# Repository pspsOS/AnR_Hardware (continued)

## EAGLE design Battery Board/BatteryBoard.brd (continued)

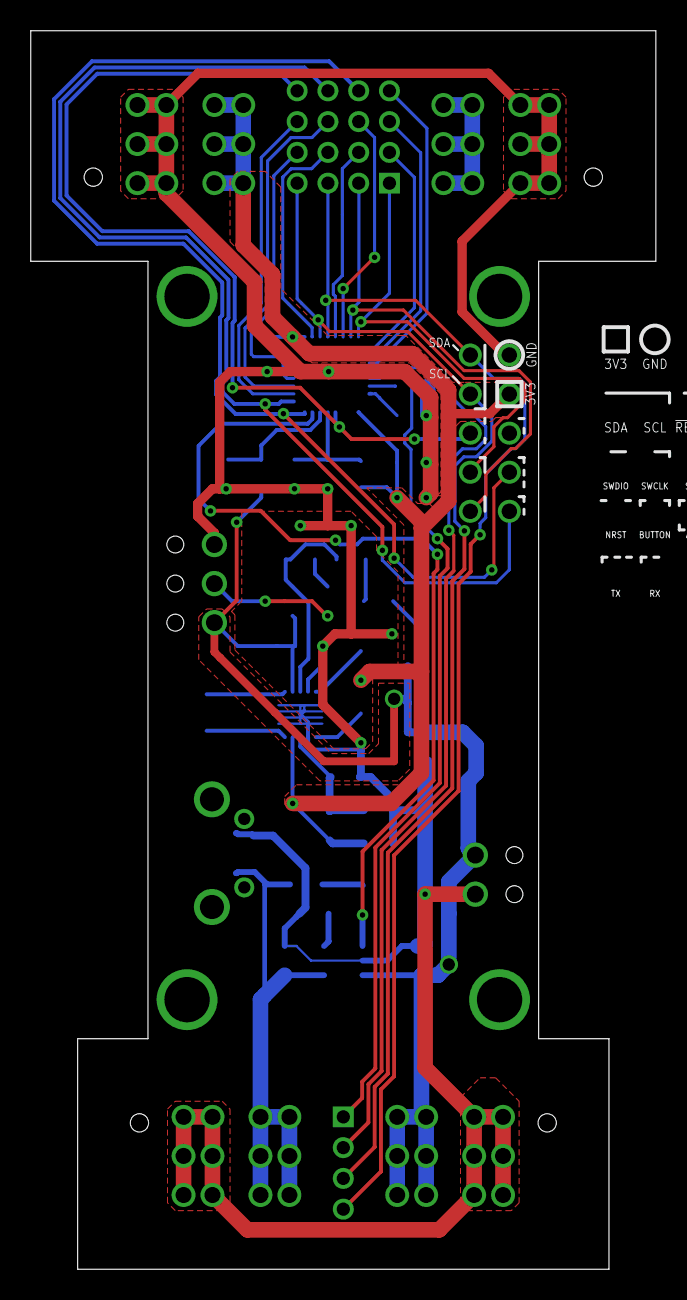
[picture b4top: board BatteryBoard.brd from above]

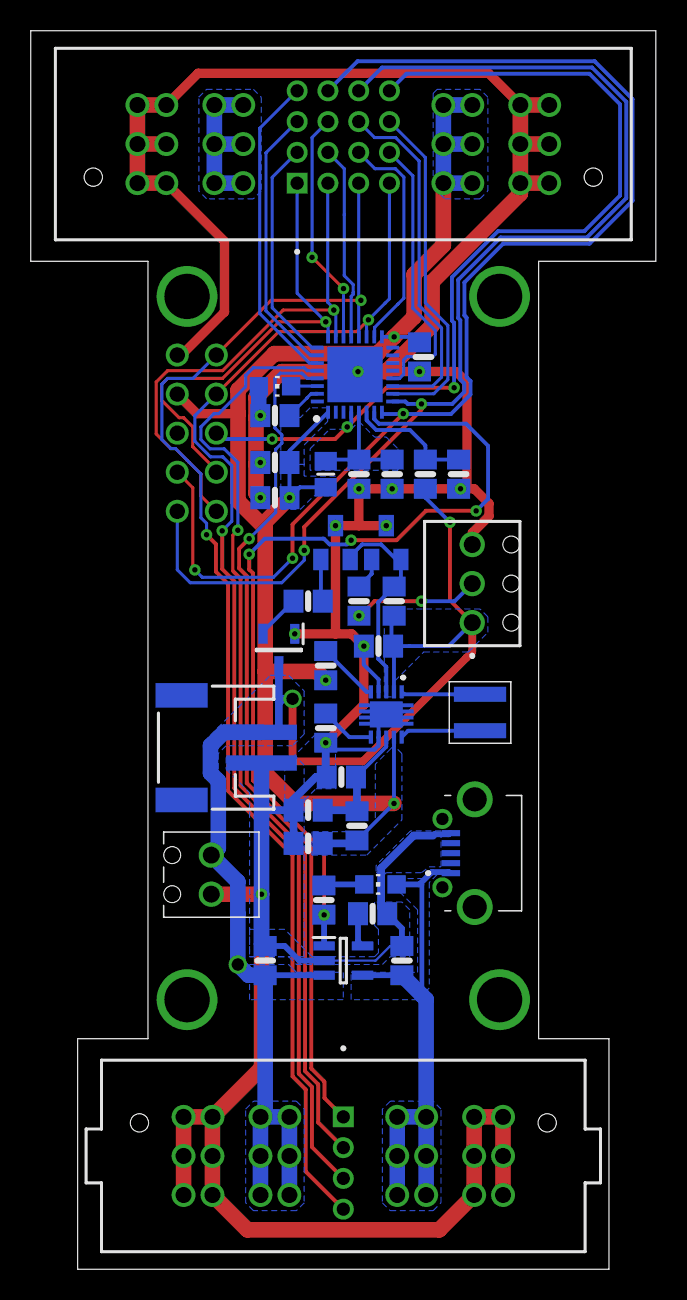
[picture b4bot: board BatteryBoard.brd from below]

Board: 2 copper layers, 40.6 x 80.5 mm, 38 parts (38 on the bottom side), 40 nets.

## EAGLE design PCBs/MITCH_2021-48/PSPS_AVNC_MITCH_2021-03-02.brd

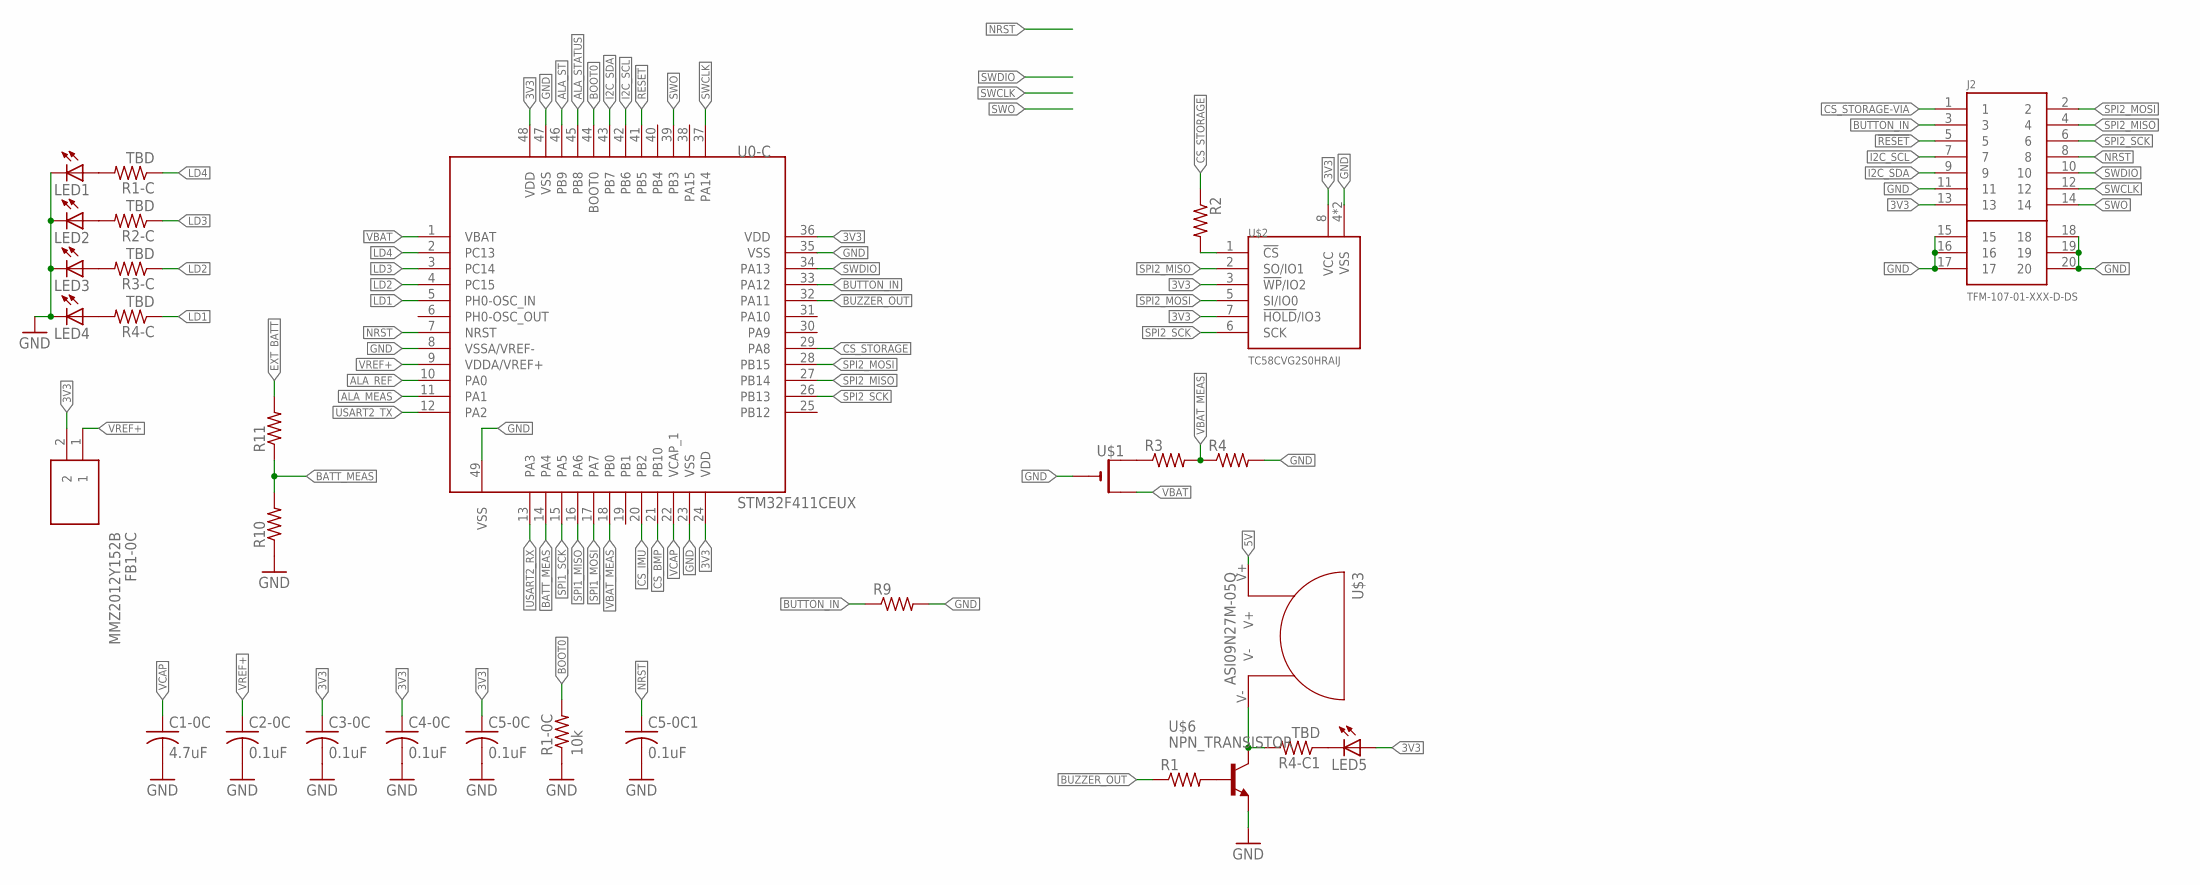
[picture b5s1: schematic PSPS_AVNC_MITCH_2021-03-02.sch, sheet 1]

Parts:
C1-0C: 4.7uF; C0805
C2-0C, C3-0C, C4-0C, C5-0C, C5-0C1: 0.1uF; C0805
FB1-0C: MMZ2012Y152B; BEADC2012X105N
J2: TFM-107-01-XXX-D-DS
LED1, LED2, LED3, LED4, LED5: LEDCHIPLED_0805; CHIPLED_0805
R1, R2, R3, R4, R9, R10, R11: R-US_R0805; R0805
R1-0C: 10k; R0805
R1-C, R2-C, R3-C, R4-C, R4-C1: TBD; R0805
U0-C: STM32F411CEUX; QFN50P700X700X50-49T560N
U$1: CR1220SMT; CR1220-SMD
U$2: TC58CVG2S0HRAIJ; SON127P800X600X80-9T350X440N
U$3: ASI09N27M-05Q
U$6: NPN_TRANSISTOR; SOT23

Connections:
3V3: C3-0C.1, C4-0C.1, C5-0C.1, FB1-0C.2, J2.13, LED5.A, U0-C.24 (VDD), U0-C.36 (VDD), U0-C.48 (VDD), U$2.3 (!WP!/IO2), U$2.7 (!HOLD!/IO3), U$2.8 (VCC); also elsewhere on the board
5V: U$3.V+; also elsewhere on the board
!RESET!: J2.5, U0-C.41 (PB5)
ALA_MEAS: U0-C.11 (PA1); also elsewhere on the board
ALA_REF: U0-C.10 (PA0); also elsewhere on the board
ALA_ST: U0-C.46 (PB9); also elsewhere on the board
ALA_STATUS: U0-C.45 (PB8); also elsewhere on the board
BATT_MEAS: R10.2, R11.1, U0-C.14 (PA4)
BOOT0: R1-0C.2, U0-C.44 (BOOT0)
BUTTON_IN: J2.3, R9.1, U0-C.33 (PA12)
BUZZER_OUT: R1.1, U0-C.32 (PA11)
CS_BMP: U0-C.21 (PB10); also elsewhere on the board
CS_IMU: U0-C.20 (PB2); also elsewhere on the board
CS_STORAGE: R2.1, U0-C.29 (PA8)
CS_STORAGE-VIA: J2.1, R2.2, U$2.1 (!CS!)
EXT_BATT: R11.2
GND: C1-0C.2, C2-0C.2, C3-0C.2, C4-0C.2, C5-0C.2, C5-0C1.2, J2.11, J2.15, J2.16, J2.17, J2.18, J2.19, J2.20, LED1.C, LED2.C, LED3.C, LED4.C, R1-0C.1, R4.2, R9.2, R10.1, U0-C.8 (VSSA/VREF-), U0-C.23 (VSS), U0-C.35 (VSS), U0-C.47 (VSS), U0-C.49 (VSS), U$1.-, U$2.4 (VSS), U$2.9 (VSS), U$6.3 (E); also elsewhere on the board
I2C_SCL: J2.7, U0-C.42 (PB6)
I2C_SDA: J2.9, U0-C.43 (PB7)
LD1: R4-C.1, U0-C.5 (PH0-OSC_IN)
LD2: R3-C.1, U0-C.4 (PC15)
LD3: R2-C.1, U0-C.3 (PC14)
LD4: R1-C.1, U0-C.2 (PC13)
unnamed: R1.2, U$6.1 (B)
unnamed: LED4.A, R4-C.2
unnamed: LED3.A, R3-C.2
unnamed: LED2.A, R2-C.2
unnamed: LED1.A, R1-C.2
unnamed: R3.1, U$1.+$1 (+)
unnamed: R4-C1.2, U$3.V-, U$6.2 (C)
unnamed: LED5.C, R4-C1.1
NRST: C5-0C1.1, J2.8, U0-C.7 (NRST)
SPI1_MISO: U0-C.16 (PA6); also elsewhere on the board
SPI1_MOSI: U0-C.17 (PA7); also elsewhere on the board
SPI1_SCK: U0-C.15 (PA5); also elsewhere on the board
SPI2_MISO: J2.4, U0-C.27 (PB14), U$2.2 (SO/IO1)
SPI2_MOSI: J2.2, U0-C.28 (PB15), U$2.5 (SI/IO0)
SPI2_SCK: J2.6, U0-C.26 (PB13), U$2.6 (SCK)
SWCLK: J2.12, U0-C.37 (PA14)
SWDIO: J2.10, U0-C.34 (PA13)
SWO: J2.14, U0-C.39 (PB3)
USART2_RX: U0-C.13 (PA3); also elsewhere on the board
USART2_TX: U0-C.12 (PA2); also elsewhere on the board
VBAT: U0-C.1 (VBAT), U$1.+$2 (+1); also elsewhere on the board
VBAT_MEAS: R3.2, R4.1, U0-C.18 (PB0)
VCAP: C1-0C.1, U0-C.22 (VCAP_1)
VREF+: C2-0C.1, FB1-0C.1, U0-C.9 (VDDA/VREF+)

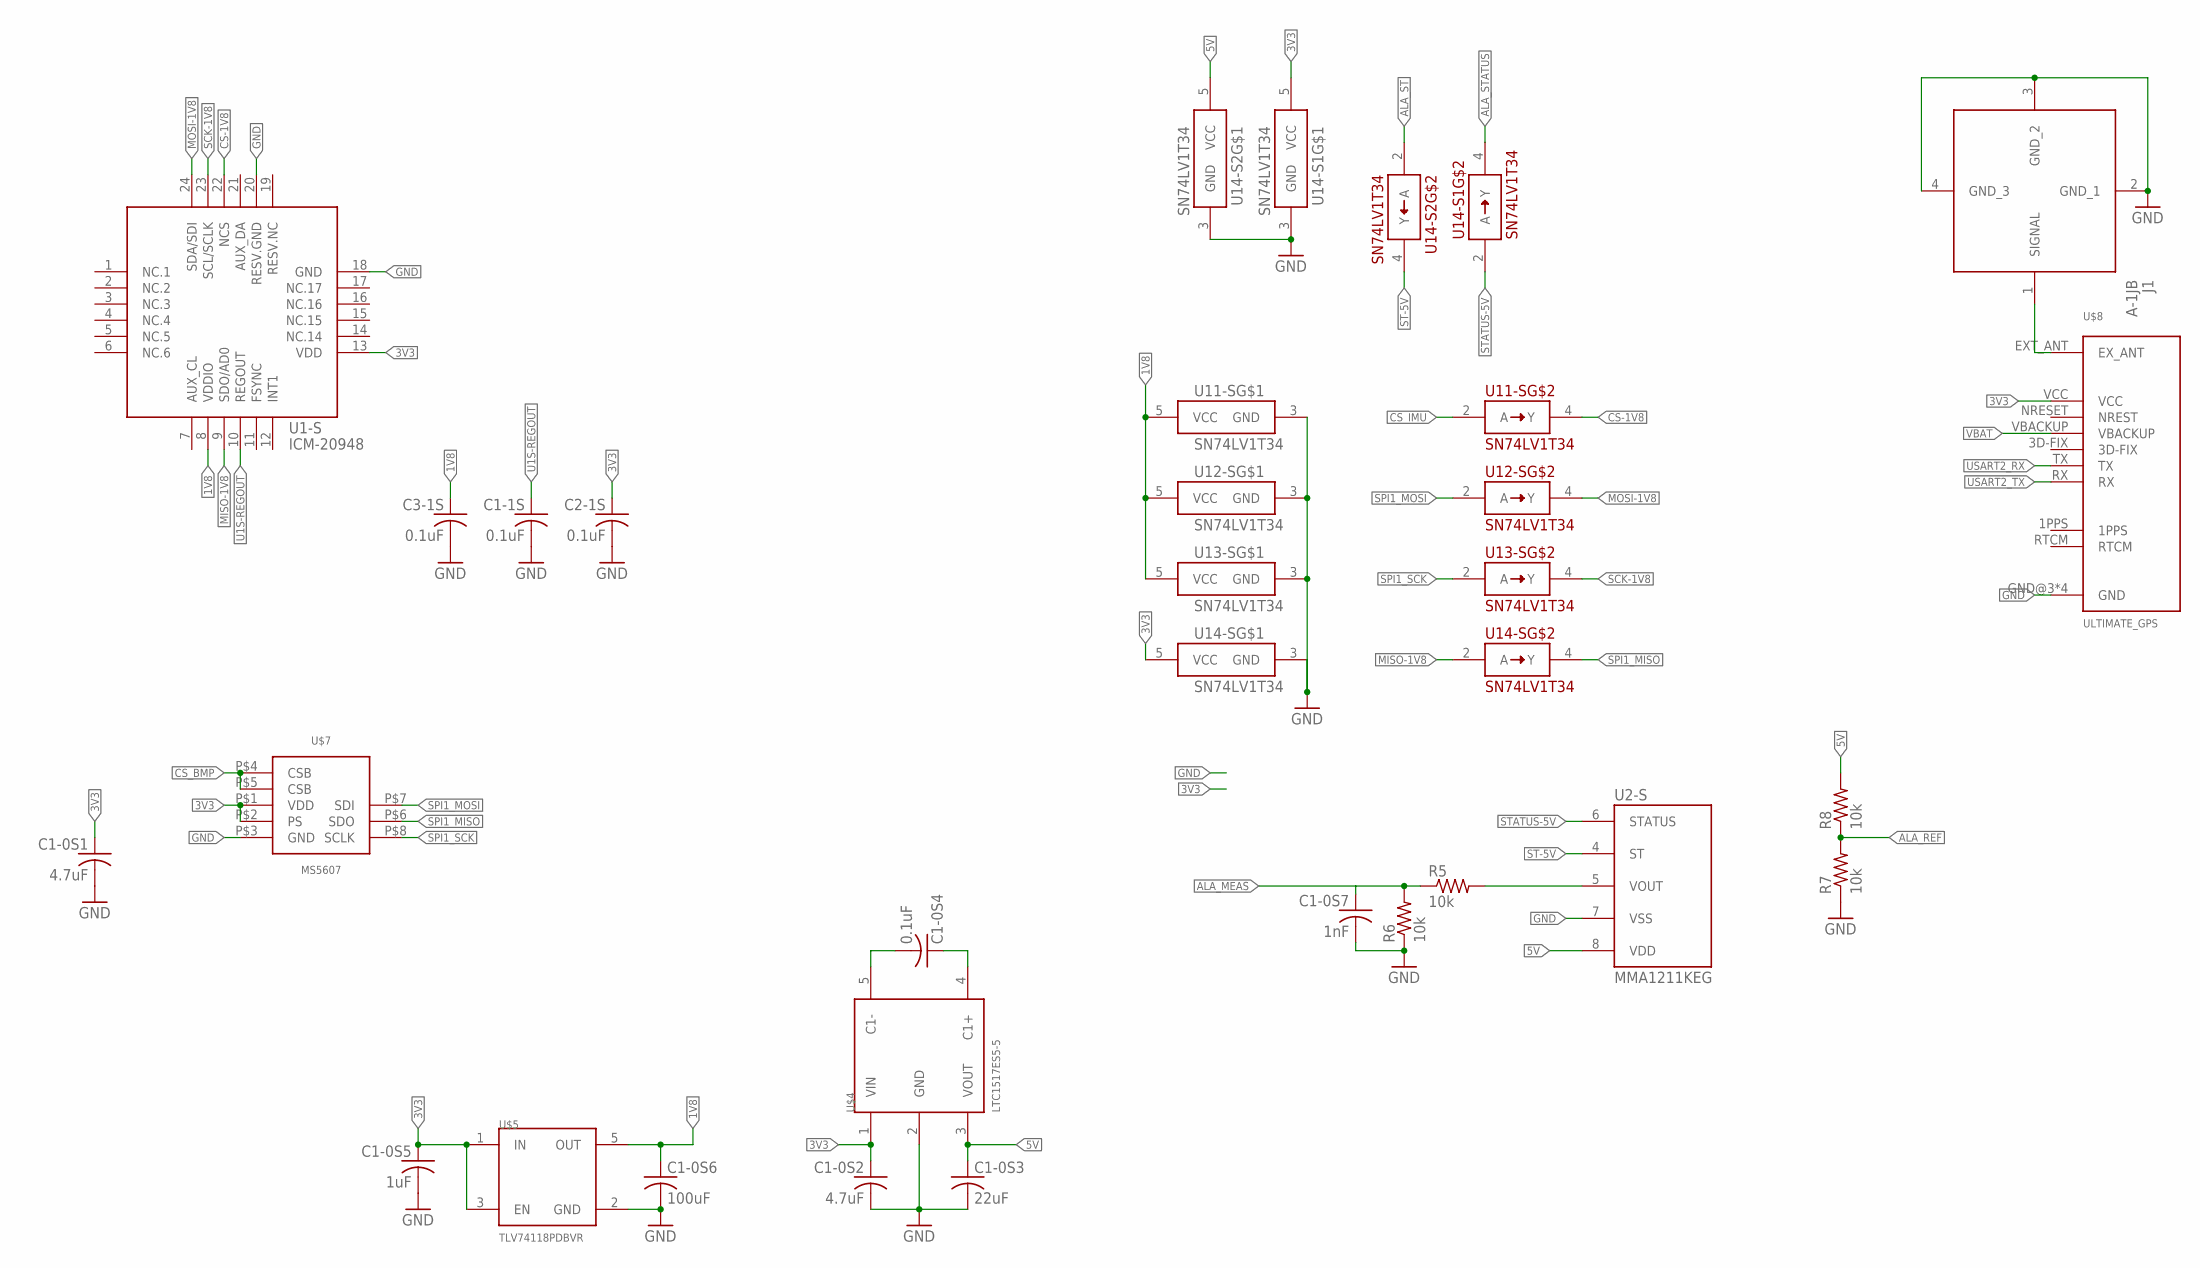
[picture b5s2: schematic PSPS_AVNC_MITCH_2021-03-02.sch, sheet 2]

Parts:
C1-0S1, C1-0S2: 4.7uF; C0805
C1-0S3: 22uF; C0805
C1-0S4, C1-1S, C2-1S, C3-1S: 0.1uF; C0805
C1-0S5: 1uF; C0805
C1-0S6: 100uF; C0805
C1-0S7: 1nF; C0805
J1: A-1JB; A1JB
R5, R6, R7, R8: 10k; R0805
U1-S: ICM-20948; QFN40P300X300X105-25T159X175
U2-S: MMA1211KEG; SOIC127P1041X355-16N
U11-S, U12-S, U13-S, U14-S, U14-S1, U14-S2: SN74LV1T34; SOT65P210X110-5
U$4: LTC1517ES5-5; SOT95P280X145-5N
U$5: TLV74118PDBVR; SOT95P280X145-5N
U$7: MS5607
U$8: ULTIMATE_GPS; FGPMMOPA6H

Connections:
1V8: C1-0S6.1, C3-1S.1, U1-S.8 (VDDIO), U11-S.5 (VCC), U12-S.5 (VCC), U13-S.5 (VCC), U$5.5 (OUT)
3V3: C1-0S1.1, C1-0S2.1, C1-0S5.1, C2-1S.1, U1-S.13 (VDD), U14-S.5 (VCC), U14-S1.5 (VCC), U$4.1 (VIN), U$5.1 (IN), U$5.3 (EN), U$7.P$1 (VDD), U$7.P$2 (PS), U$8.VCC; also elsewhere on the board
5V: C1-0S3.1, R8.2, U2-S.8 (VDD), U14-S2.5 (VCC), U$4.3 (VOUT); also elsewhere on the board
ALA_MEAS: C1-0S7.1, R5.1, R6.2; also elsewhere on the board
ALA_REF: R7.2, R8.1; also elsewhere on the board
ALA_ST: U14-S2.2 (A); also elsewhere on the board
ALA_STATUS: U14-S1.4 (Y); also elsewhere on the board
CS-1V8: U1-S.22 (NCS), U11-S.4 (Y)
CS_BMP: U$7.P$4 (CSB), U$7.P$5 (CSB); also elsewhere on the board
CS_IMU: U11-S.2 (A); also elsewhere on the board
GND: C1-0S1.2, C1-0S2.2, C1-0S3.2, C1-0S5.2, C1-0S6.2, C1-0S7.2, C1-1S.2, C2-1S.2, C3-1S.2, J1.2 (GND_1), J1.3 (GND_2), J1.4 (GND_3), R6.1, R7.1, U1-S.18 (GND), U1-S.20 (RESV.GND), U2-S.7 (VSS), U11-S.3 (GND), U12-S.3 (GND), U13-S.3 (GND), U14-S.3 (GND), U14-S1.3 (GND), U14-S2.3 (GND), U$4.2 (GND), U$5.2 (GND), U$7.P$3 (GND), U$8.GND@3 (GND), U$8.GND@8 (GND), U$8.GND@12 (GND), U$8.GND@19 (GND); also elsewhere on the board
MISO-1V8: U1-S.9 (SDO/AD0), U14-S.2 (A)
MOSI-1V8: U1-S.24 (SDA/SDI), U12-S.4 (Y)
unnamed: C1-0S4.1, U$4.4 (C1+)
unnamed: C1-0S4.2, U$4.5 (C1-)
unnamed: J1.1 (SIGNAL), U$8.EXT_ANT (EX_ANT)
unnamed: R5.2, U2-S.5 (VOUT)
SCK-1V8: U1-S.23 (SCL/SCLK), U13-S.4 (Y)
SPI1_MISO: U14-S.4 (Y), U$7.P$6 (SDO); also elsewhere on the board
SPI1_MOSI: U12-S.2 (A), U$7.P$7 (SDI); also elsewhere on the board
SPI1_SCK: U13-S.2 (A), U$7.P$8 (SCLK); also elsewhere on the board
ST-5V: U2-S.4 (ST), U14-S2.4 (Y)
STATUS-5V: U2-S.6 (STATUS), U14-S1.2 (A)
U1S-REGOUT: C1-1S.1, U1-S.10 (REGOUT)
USART2_RX: U$8.TX; also elsewhere on the board
USART2_TX: U$8.RX; also elsewhere on the board
VBAT: U$8.VBACKUP; also elsewhere on the board

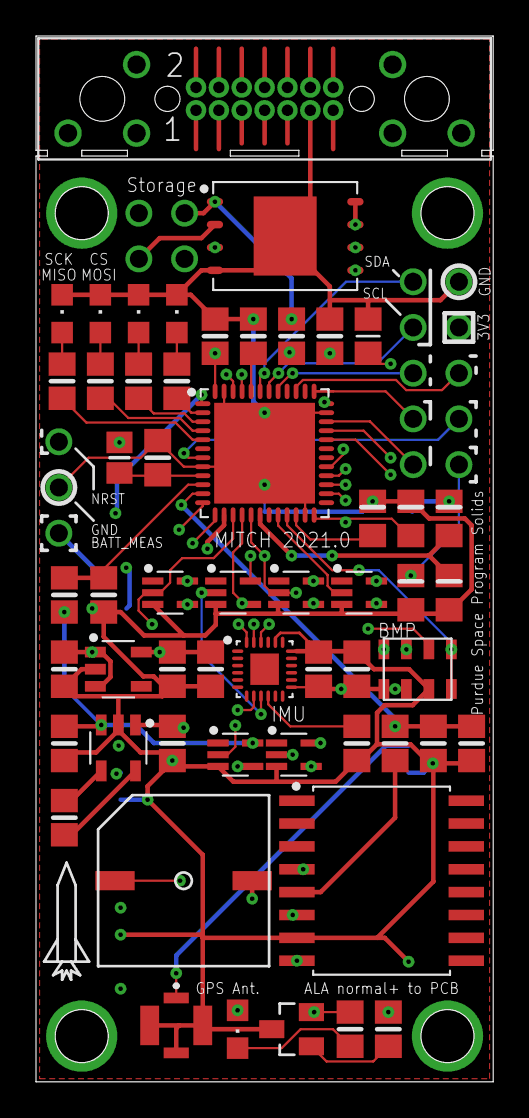
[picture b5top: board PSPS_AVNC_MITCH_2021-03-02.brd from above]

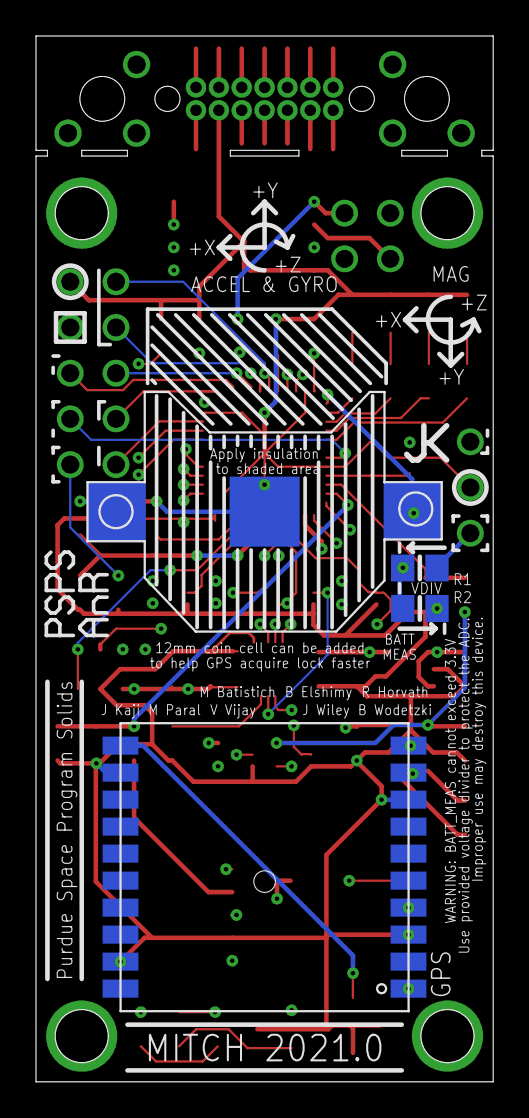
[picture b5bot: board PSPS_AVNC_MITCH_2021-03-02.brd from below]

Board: 4 copper layers, 25.4 x 58.1 mm, 58 parts (4 on the bottom side), 58 nets.

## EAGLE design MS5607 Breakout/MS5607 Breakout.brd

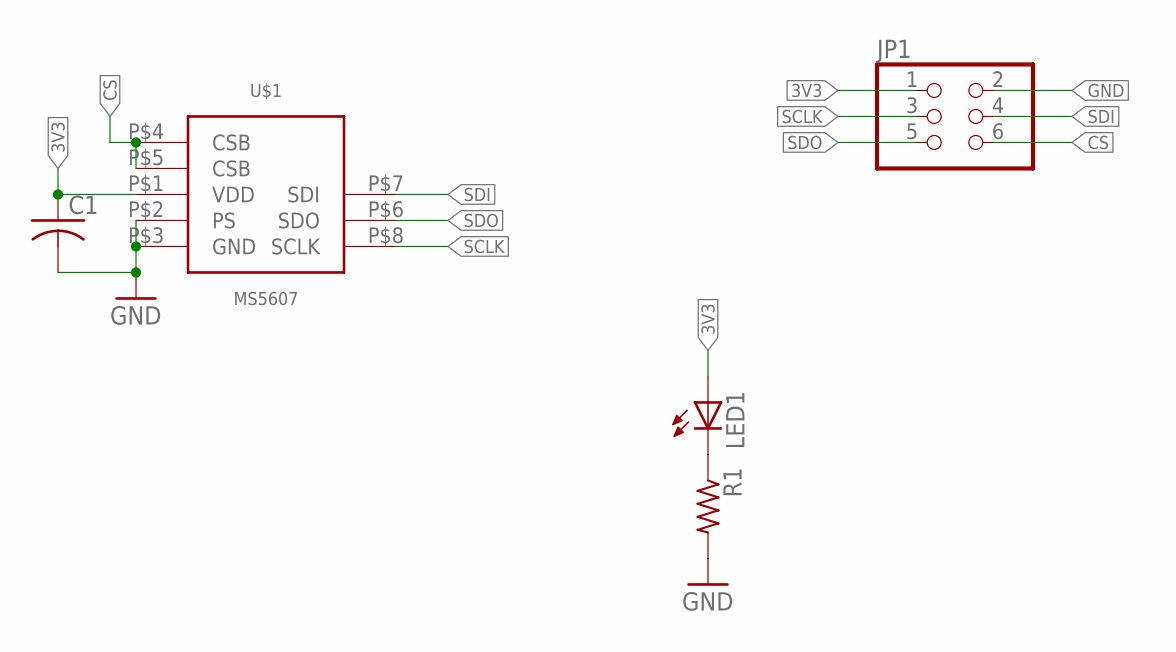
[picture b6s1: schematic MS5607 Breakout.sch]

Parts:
C1: C-USC0805; C0805
JP1: PINHD-2X3; 2X03
LED1: LEDCHIPLED_0805; CHIPLED_0805
R1: R-US_R0805; R0805
U$1: MS5607

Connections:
3V3: C1.1, JP1.1, LED1.A, U$1.P$1 (VDD)
CS: JP1.6, U$1.P$4 (CSB), U$1.P$5 (CSB)
GND: C1.2, JP1.2, R1.2, U$1.P$2 (PS), U$1.P$3 (GND)
unnamed: LED1.C, R1.1
SCLK: JP1.3, U$1.P$8 (SCLK)
SDI: JP1.4, U$1.P$7 (SDI)
SDO: JP1.5, U$1.P$6 (SDO)

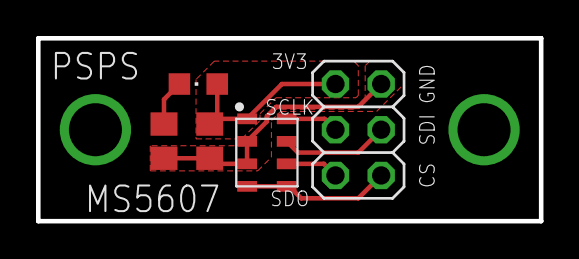
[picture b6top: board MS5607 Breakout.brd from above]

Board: 2 copper layers, 27.9 x 10.2 mm, 5 parts (0 on the bottom side), 7 nets.

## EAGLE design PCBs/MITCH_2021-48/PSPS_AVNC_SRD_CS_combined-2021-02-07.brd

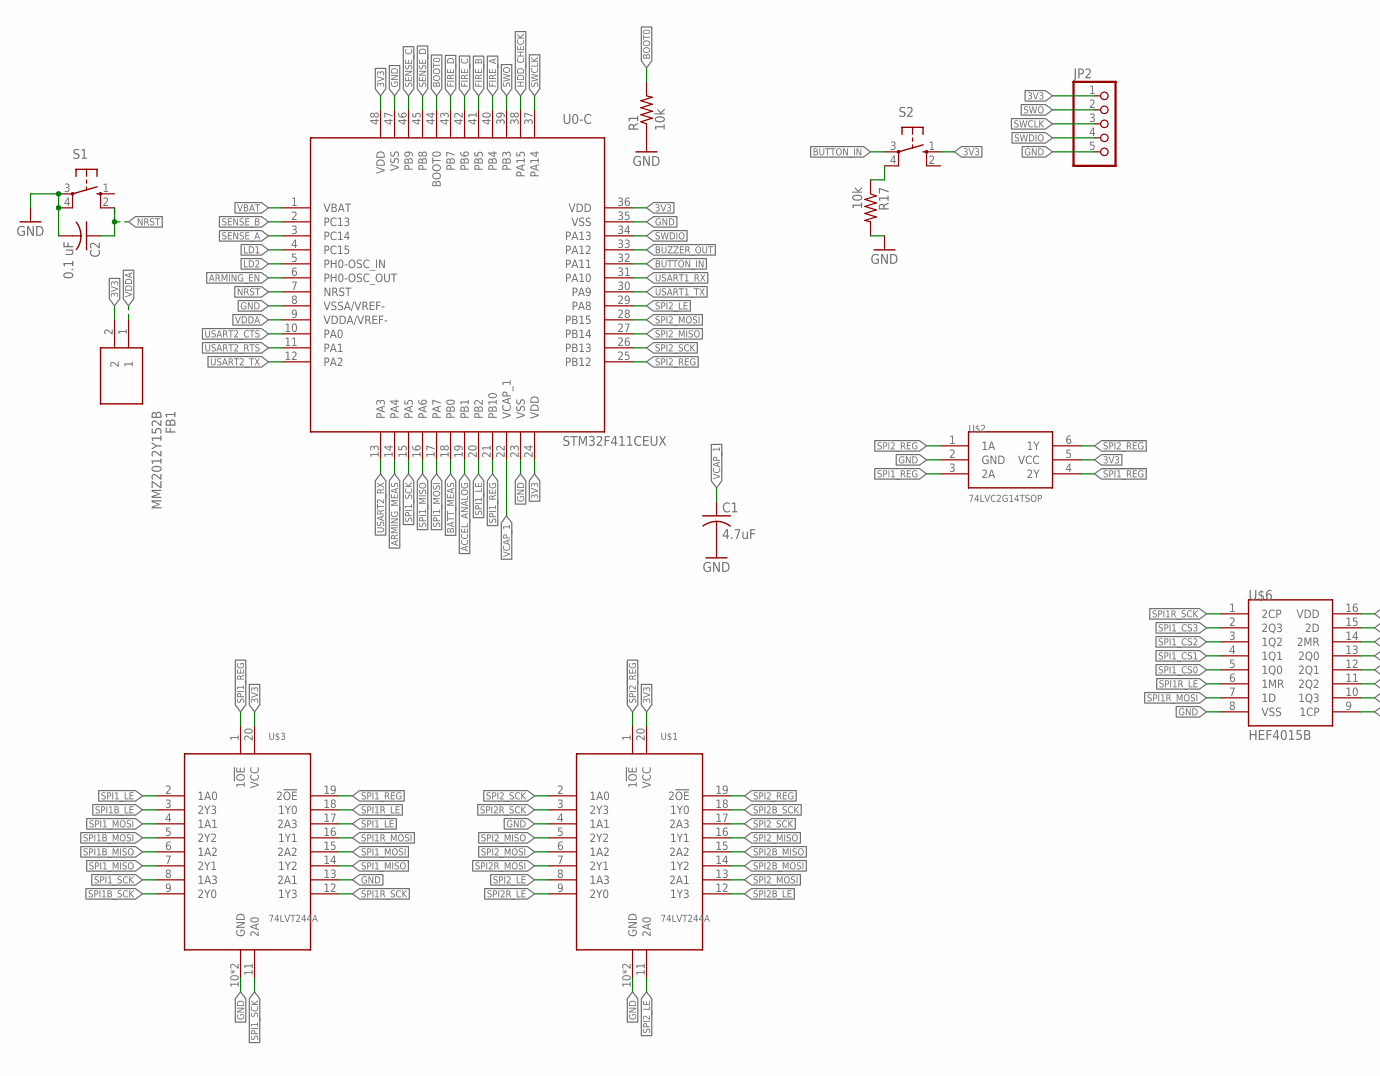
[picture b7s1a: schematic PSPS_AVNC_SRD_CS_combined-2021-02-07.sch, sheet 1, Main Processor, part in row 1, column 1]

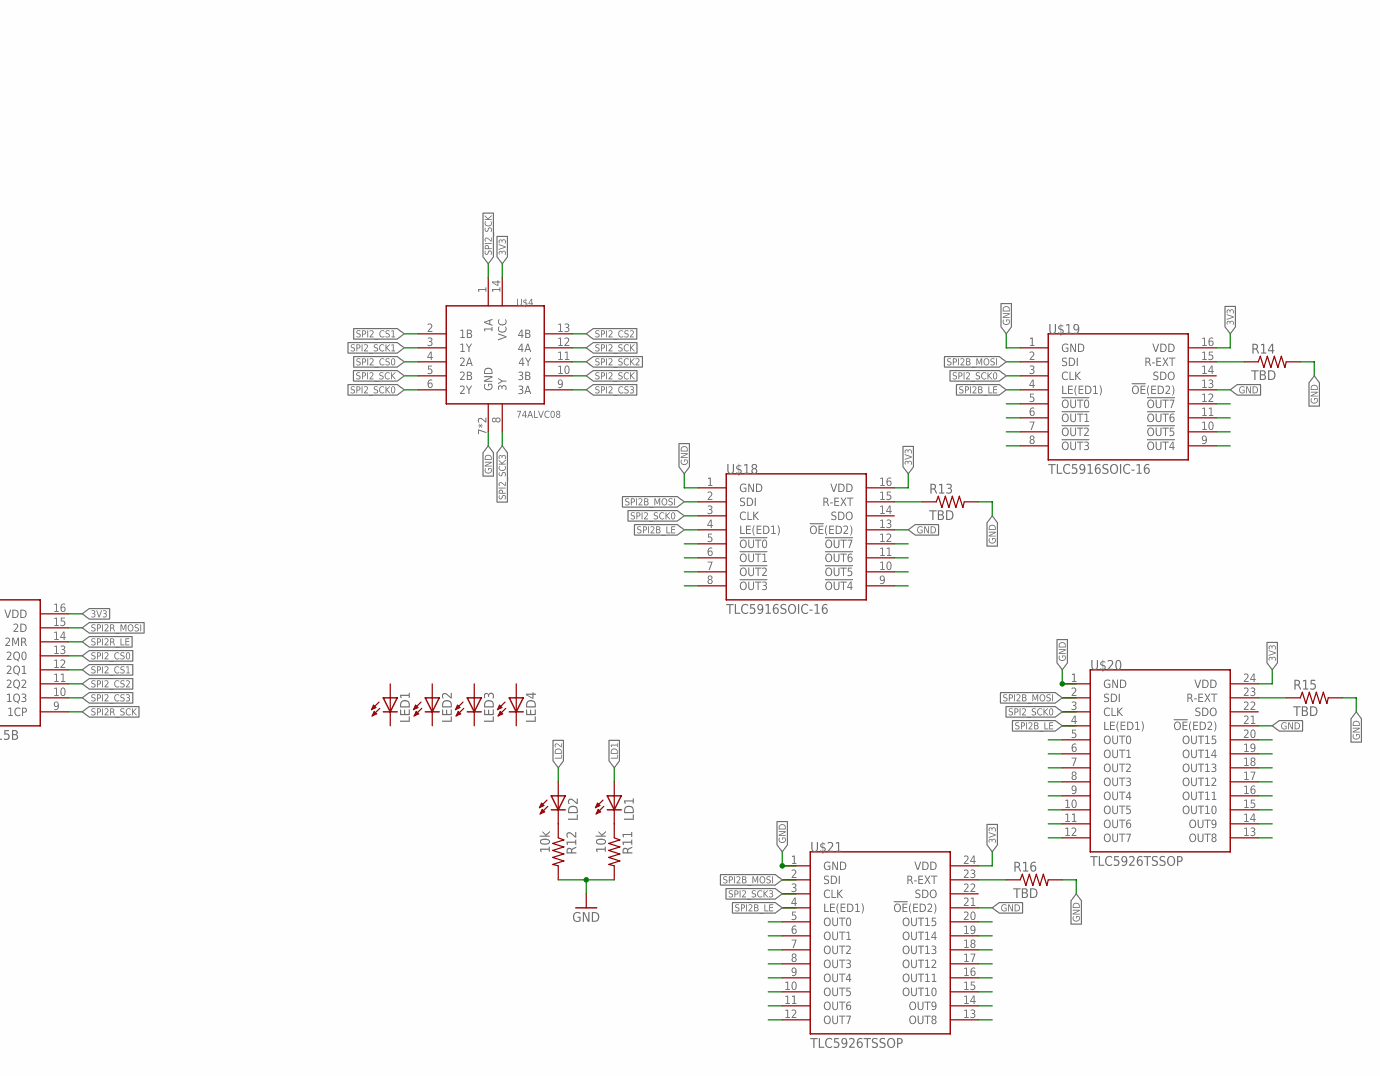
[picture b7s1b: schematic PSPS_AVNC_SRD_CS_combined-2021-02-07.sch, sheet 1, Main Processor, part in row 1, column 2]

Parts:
C1: 4.7uF; C0805
C2: 0.1 uF; C0805
FB1: MMZ2012Y152B; BEADC2012X105N
JP2: PINHD-1X5; 1X05
LD1, LD2: LEDCHIP-LED0805; CHIP-LED0805
LED1, LED2, LED3, LED4: LEDCHIP-LED0805; CHIP-LED0805
R1, R11, R12, R17: 10k; M0805
R13, R14, R15, R16: TBD; M0805
S1, S2: 10-XX; B3F-10XX
U0-C: STM32F411CEUX; QFN50P700X700X50-49T560N
U$1, U$3: 74LVT244A; QFN50P450X250X100-21T300X100N
U$2: 74LVC2G14TSOP; SOP95P280X110-6N
U$4: 74ALVC08; QFN50P300X250X100-15T150X100N
U$6: HEF4015B; SOIC127P600X265-16N
U$18, U$19: TLC5916SOIC-16; SOIC127P600X175-16N
U$20, U$21: TLC5926TSSOP; SOP65P640X120-24N

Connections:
3V3: FB1.2, JP2.1, S2.1 (S), U0-C.24 (VDD), U0-C.36 (VDD), U0-C.48 (VDD), U$1.20 (VCC), U$2.5 (VCC), U$3.20 (VCC), U$4.14 (VCC), U$6.16 (VDD), U$18.16 (VDD), U$19.16 (VDD), U$20.24 (VDD), U$21.24 (VDD); also elsewhere on the board
!SPI1_REG!: U$2.4 (2Y), U$3.19 (2!OE!)
!SPI2_REG!: U$1.1 (1!OE!), U$2.6 (1Y)
ACCEL_ANALOG: U0-C.19 (PB1); also elsewhere on the board
ARMING_EN: U0-C.6 (PH0-OSC_OUT)
ARMING_MEAS: U0-C.14 (PA4)
BATT_MEAS: U0-C.18 (PB0)
BOOT0: R1.2, U0-C.44 (BOOT0)
BUTTON_IN: S2.3, U0-C.32 (PA11)
BUZZER_OUT: U0-C.33 (PA12); also elsewhere on the board
FIRE_A: U0-C.40 (PB4)
FIRE_B: U0-C.41 (PB5)
FIRE_C: U0-C.42 (PB6)
FIRE_D: U0-C.43 (PB7)
GND: C1.2, C2.2, JP2.5, R1.1, R11.2, R12.2, R13.2, R14.2, R15.2, R16.2, R17.2, S1.3, S1.4 (P1), U0-C.8 (VSSA/VREF-), U0-C.23 (VSS), U0-C.35 (VSS), U0-C.47 (VSS), U$1.4 (1A1), U$1.10 (GND), U$1.21 (GND), U$2.2 (GND), U$3.10 (GND), U$3.13 (2A1), U$3.21 (GND), U$4.7 (GND), U$4.15 (GND), U$6.8 (VSS), U$18.1 (GND), U$18.13 (!OE!(ED2)), U$19.1 (GND), U$19.13 (!OE!(ED2)), U$20.1 (GND), U$20.21 (!OE!(ED2)), U$21.1 (GND), U$21.21 (!OE!(ED2)); also elsewhere on the board
HDD_CHECK: U0-C.38 (PA15)
LD1: LD1.A, U0-C.4 (PC15)
LD2: LD2.A, U0-C.5 (PH0-OSC_IN)
unnamed: LD1.C, R11.1
unnamed: LD2.C, R12.1
unnamed: R13.1, U$18.15 (R-EXT)
unnamed: R14.1, U$19.15 (R-EXT)
unnamed: R15.1, U$20.23 (R-EXT)
unnamed: R16.1, U$21.23 (R-EXT)
unnamed: R17.1, S2.4 (P1)
NRST: C2.1, S1.2 (S1), U0-C.7 (NRST)
SENSE_A: U0-C.3 (PC14)
SENSE_B: U0-C.2 (PC13)
SENSE_C: U0-C.46 (PB9)
SENSE_D: U0-C.45 (PB8)
SPI1B_LE: U$3.3 (2Y3); also elsewhere on the board
SPI1B_MISO: U$3.6 (1A2); also elsewhere on the board
SPI1B_MOSI: U$3.5 (2Y2); also elsewhere on the board
SPI1B_SCK: U$3.9 (2Y0); also elsewhere on the board
SPI1R_LE: U$3.18 (1Y0), U$6.6 (1MR)
SPI1R_MOSI: U$3.16 (1Y1), U$6.7 (1D)
SPI1R_SCK: U$3.12 (1Y3), U$6.1 (2CP)
SPI1_CS0: U$6.5 (1Q0); also elsewhere on the board
SPI1_CS1: U$6.4 (1Q1); also elsewhere on the board
SPI1_CS2: U$6.3 (1Q2); also elsewhere on the board
SPI1_CS3: U$6.2 (2Q3)
SPI1_LE: U0-C.20 (PB2), U$3.2 (1A0), U$3.17 (2A3)
SPI1_MISO: U0-C.16 (PA6), U$3.7 (2Y1), U$3.14 (1Y2)
SPI1_MOSI: U0-C.17 (PA7), U$3.4 (1A1), U$3.15 (2A2)
SPI1_REG: U0-C.21 (PB10), U$2.3 (2A), U$3.1 (1!OE!)
SPI1_SCK: U0-C.15 (PA5), U$3.8 (1A3), U$3.11 (2A0)
SPI2B_LE: U$1.12 (1Y3), U$18.4 (LE(ED1)), U$19.4 (LE(ED1)), U$20.4 (LE(ED1)), U$21.4 (LE(ED1))
SPI2B_MISO: U$1.15 (2A2)
SPI2B_MOSI: U$1.14 (1Y2), U$18.2 (SDI), U$19.2 (SDI), U$20.2 (SDI), U$21.2 (SDI)
SPI2B_SCK: U$1.18 (1Y0)
SPI2R_LE: U$1.9 (2Y0), U$6.14 (2MR)
SPI2R_MOSI: U$1.7 (2Y1), U$6.15 (2D)
SPI2R_SCK: U$1.3 (2Y3), U$6.9 (1CP)
SPI2_CS0: U$4.4 (2A), U$6.13 (2Q0)
SPI2_CS1: U$4.2 (1B), U$6.12 (2Q1)
SPI2_CS2: U$4.13 (4B), U$6.11 (2Q2)
SPI2_CS3: U$4.9 (3A), U$6.10 (1Q3)
SPI2_LE: U0-C.29 (PA8), U$1.8 (1A3), U$1.11 (2A0)
SPI2_MISO: U0-C.27 (PB14), U$1.5 (2Y2), U$1.16 (1Y1)
SPI2_MOSI: U0-C.28 (PB15), U$1.6 (1A2), U$1.13 (2A1)
SPI2_REG: U0-C.25 (PB12), U$1.19 (2!OE!), U$2.1 (1A)
SPI2_SCK: U0-C.26 (PB13), U$1.2 (1A0), U$1.17 (2A3), U$4.1 (1A), U$4.5 (2B), U$4.10 (3B), U$4.12 (4A)
SPI2_SCK0: U$4.6 (2Y), U$18.3 (CLK), U$19.3 (CLK), U$20.3 (CLK)
SPI2_SCK1: U$4.3 (1Y)
SPI2_SCK2: U$4.11 (4Y)
SPI2_SCK3: U$4.8 (3Y), U$21.3 (CLK)
SWCLK: JP2.3, U0-C.37 (PA14)
SWDIO: JP2.4, U0-C.34 (PA13)
SWO: JP2.2, U0-C.39 (PB3)
USART1_RX: U0-C.31 (PA10); also elsewhere on the board
USART1_TX: U0-C.30 (PA9); also elsewhere on the board
USART2_CTS: U0-C.10 (PA0)
USART2_RTS: U0-C.11 (PA1)
USART2_RX: U0-C.13 (PA3)
USART2_TX: U0-C.12 (PA2)
VBAT: U0-C.1 (VBAT); also elsewhere on the board
VCAP_1: C1.1, U0-C.22 (VCAP_1)
VDDA: FB1.1, U0-C.9 (VDDA/VREF-)
